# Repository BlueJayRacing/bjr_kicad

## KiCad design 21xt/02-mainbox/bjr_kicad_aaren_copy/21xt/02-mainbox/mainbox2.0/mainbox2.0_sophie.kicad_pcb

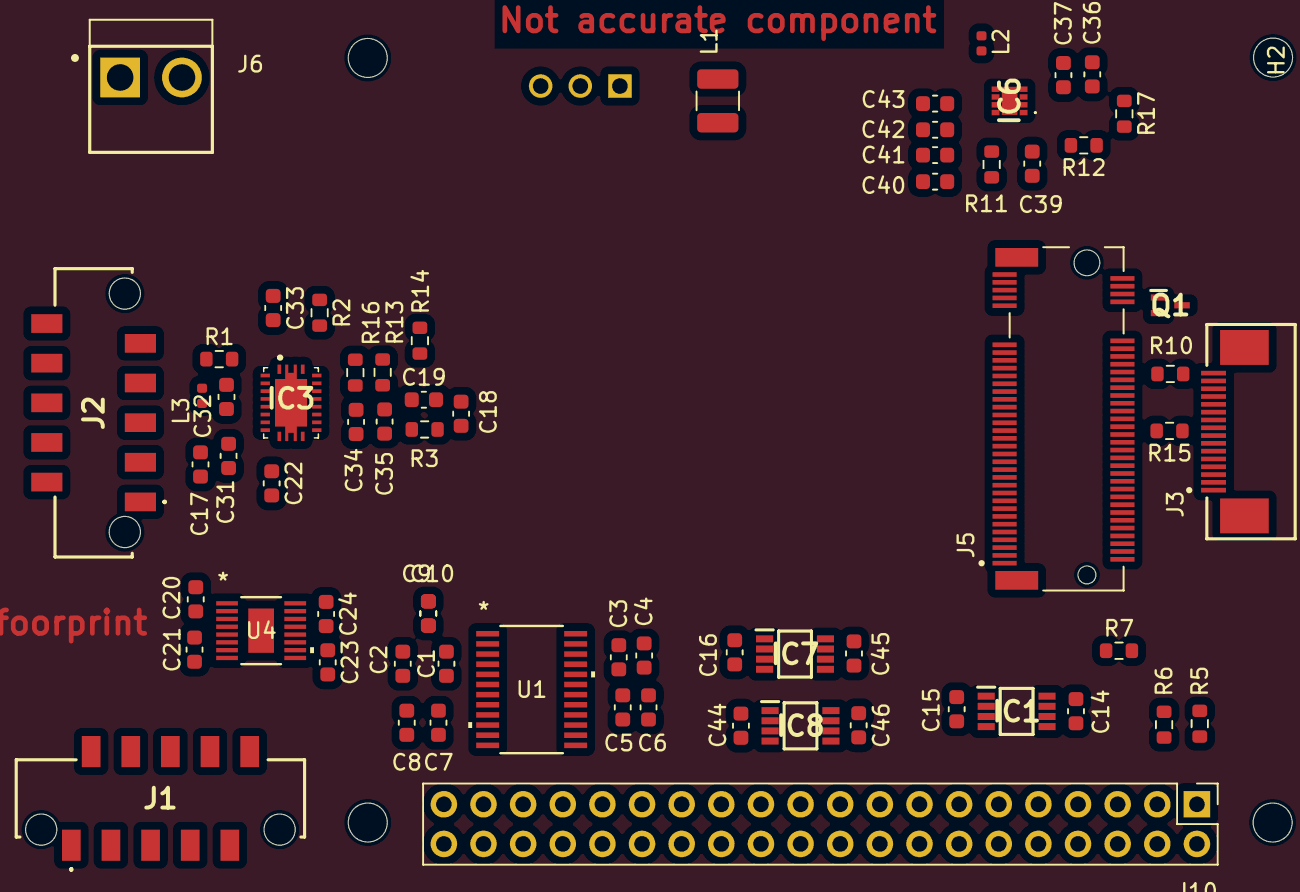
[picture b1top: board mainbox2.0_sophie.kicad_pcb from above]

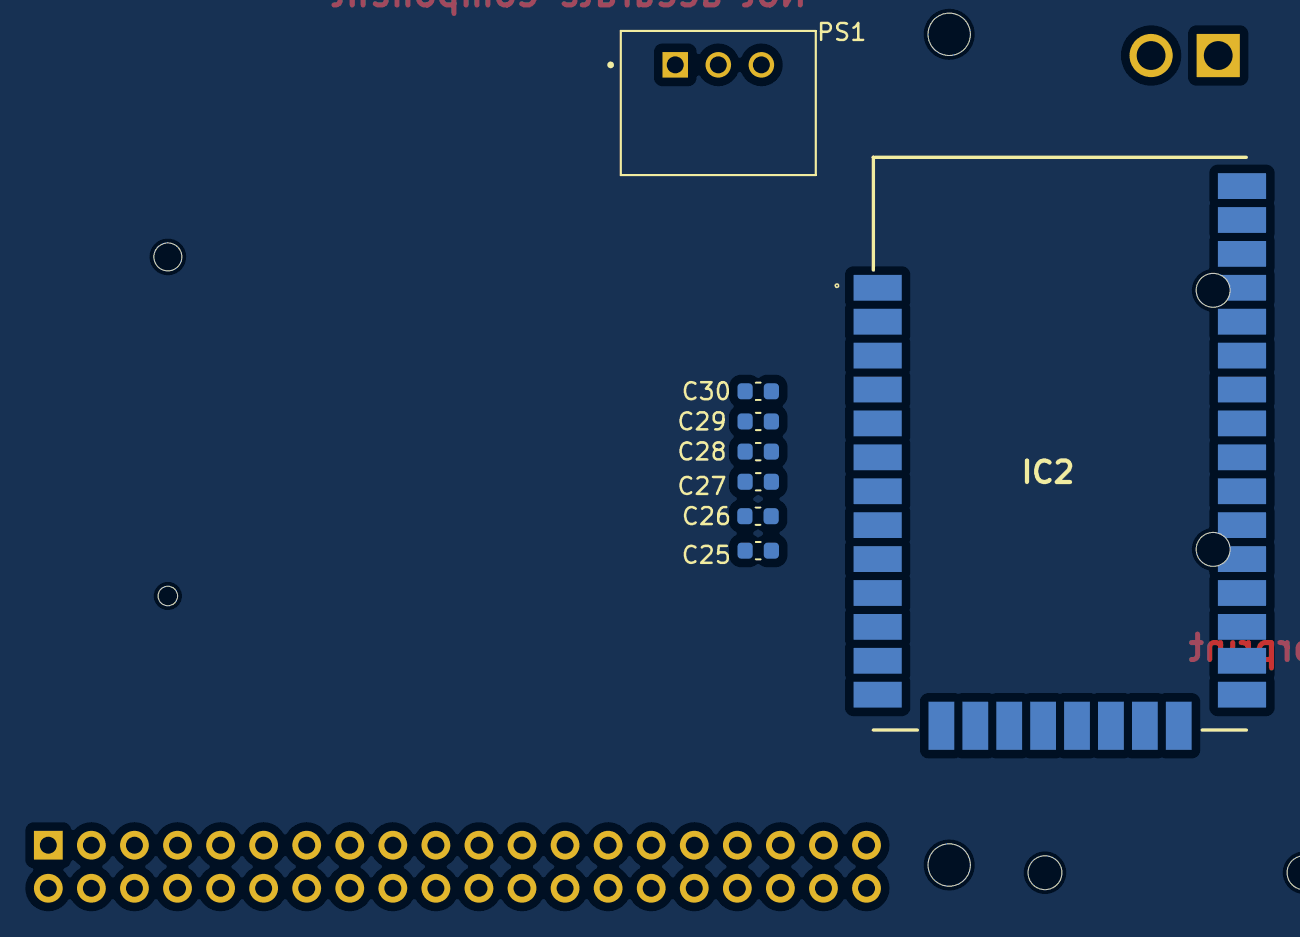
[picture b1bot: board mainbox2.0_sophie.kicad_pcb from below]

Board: 4 copper layers, 79 parts (8 on the bottom side), 57 nets, no tracks yet.

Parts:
C1, C3, C5, C7, C10, C14, C15, C16, C17, C20, C21, C23, C27, C31, C32, C44, C45, C46: 0.1uF; C_0603_1608Metric
C2, C4, C8, C24, C34: 1uF; C_0603_1608Metric
C6, C9, C25, C28, C36, C37, C40, C41, C42, C43: 10uF; C_0603_1608Metric
C18: 0.6nF; C_0603_1608Metric
C19: 3.1pF; C_0603_1608Metric
C22: 47nF; C_0603_1608Metric
C26: 4.7uF; C_0603_1608Metric
C29: 47pF; C_0603_1608Metric
C30: 8.2pF; C_0603_1608Metric
C33: 3.3uF; C_0603_1608Metric
C35: 47uF; C_0603_1608Metric
C39: 15pF; C_0603_1608Metric
H1, H2, H3, H4: MountingHole; MountingHole_2.5mm
IC1, IC7, IC8: SN74LVC2T45DCTTG4; SOP65P400X130-8N
IC2: XBP9X-DMUS-011; RLS397
IC3: TPS61088QRHLTQ1; BQ24123RHLT
IC6: AP3441LSHE-7B; AP3441LSHE7B
J1, J2: Conn_01x10; 908160010(picolex-10)
J3: Conn_01x16; SAMTEC_ZF5S-16-01-T-WT
J5: MDT275M02001; AMPHENOL_MDT275M02001
J6: Conn_01x02; JST_B2P-VH_LF__SN_(2 pin)
J10: Conn_02x20_Odd_Even; PinHeader_2x20_P2.54mm_Vertical
L1: 3.9uH; L_1210_3225Metric
L2: 22uH; L_0402_1005Metric
L3: 1.2uH; L_0402_1005Metric
PS1: R-78B3.3-1.5L; CONV_R-78B3.3-1.5
Q1: DMG1012T-7; SOT50P160X90-3N(DIODE)
R1: 225k; R_0603_1608Metric
R2: 49.9k; R_0603_1608Metric
R3: 125k; R_0603_1608Metric
R5, R6: 68; R_0603_1608Metric
R7, R15: 100k; R_0603_1608Metric
R10: 33; R_0603_1608Metric
R11, R17: 10k; R_0603_1608Metric
R12: 22k; R_0603_1608Metric
R13: 290k; R_0603_1608Metric
R14: 56k; R_0603_1608Metric
R16: 60k; R_0603_1608Metric
U1: AD7175-2BRUZ; RU_24_ADI
U4: LT6658AHMSE-5-PBF; LT6658AHMSE-2.5-PBF

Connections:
3V3: C5.1, C6.1, C14.2, C16.2, C44.2, IC1.8 (VCCB), IC7.1 (VCCA), IC8.1 (VCCA), J10.17, U1.16 (IOVDD)
3V3_PG: IC6.2 (PG), Q1.1 (G), R17.2
3V3_XBEE: C27.2, C28.2, C29.2, C30.2, IC2.2 (VCC), PS1.3 (+VOUT)
5.2V: C15.2, C25.1, C26.1, C36.1, C37.1, C45.2, C46.2, IC1.1 (VCCA), IC6.3 (VIN), IC7.8 (VCCB), IC8.8 (VCCB), J1.7, J6.2, J10.2, J10.4, L1.1, R17.1
5VADC/SENSOR: C7.2, C8.2, J2.6, U1.7 (AVDD1), U1.8 (AVDD2), U4.7 (VOUT2_S), U4.8 (VOUT2_F)
5VRef: C9.2, C10.2, C24.2, U1.3 (REF+), U4.12 (VOUT1_F), U4.13 (VOUT1_S)
7.5VBOOST: C23.1, C34.2, C35.2, IC3.14 (VOUT_1), IC3.15 (VOUT_2), IC3.16 (VOUT_3), R13.1, R16.1, U4.9 (*OD), U4.10 (VIN2), U4.11 (VIN1), U4.14 (VIN)
ANI1: J2.1, U1.22 (AIN1)
ANI2: J2.2, U1.23 (AIN2)
ANI3: J2.3, U1.24 (AIN3)
ANI4: J2.4, U1.1 (AIN4)
CS: J10.24, U1.14 (*CS)
DIGITAL_INPUT_1: IC8.7 (B1), J2.7
DIGITAL_INPUT_2: IC8.6 (B2), J2.8
DIGITAL_INPUT_3: IC7.7 (B1), J2.9
DIGITAL_INPUT_4: IC7.6 (B2), J2.10
DIGITAL_OUTPUT_1: IC8.2 (A1), J10.3
DIGITAL_OUTPUT_2: IC8.3 (A2), J10.5
DIN: J10.19, U1.12 (DIN)
DINXBee: IC2.4 (DIN/DIO14/~CONFIG), R6.1, R7.1
DOUT: J10.21, U1.11 (DOUT/*RDY)
DOUTXBee: IC2.3 (DIO13/DOUT), R5.2
GND: C1.2, C2.2, C3.1, C4.1, C5.2, C6.2, C7.1, C8.1, C9.1, C10.1, C14.1, C15.1, C16.1, C17.2, C18.2, C19.2, C20.1, C21.1, C22.2, C23.2, C24.1, C25.2, C26.2, C27.1, C28.1, C29.1, C30.1, C31.2, C33.1, C34.1, C35.1, C36.2, C37.2, C40.2, C41.2, C42.2, C43.2, C44.1, C45.1, C46.1, IC1.4 (GND), IC1.5 (DIR), IC2.1 (GND_1), IC2.11 (GND_2), IC2.13 (GND_3), IC2.22 (GND_4), IC2.35 (GND_5), IC3.11 (NC_1), IC3.12 (NC_2), IC3.20 (AGND), IC3.21 (PGND_1), IC3.22 (PGND_2), IC3.23 (PGND_3), IC3.24 (PGND_4), IC3.25 (PGND_5), IC3.26 (PGND_6), IC3.27 (PGND_7), IC6.4 (PGND), IC6.8 (SGND), IC6.9 (EP), IC7.4 (GND), IC7.5 (DIR), IC8.4 (GND), IC8.5 (DIR), J1.8, J2.5, J3.12, J5.1, J5.3, J5.9, J5.15, J5.21, J5.27, J5.33, J5.39, J5.45, J5.51, J5.57, J5.71, J5.73, J5.75, J6.1, J10.6, J10.9, PS1.2 (GND), R2.1, R12.1, R14.2, R15.2, U1.2 (REF-), U1.6 (AVSS), U1.15 (*SYNC/*ERROR), U1.17 (DGND), U4.1 (GND), U4.2 (GND), U4.6 (GND), U4.EPAD
IN1(3.3V): IC1.7 (B1), J10.11
IN1(5V): IC1.2 (A1), J1.9
IN2(3.3V): IC1.6 (B2), J10.13
IN2(5V): IC1.3 (A2), J1.10
unnamed: C18.1, R3.2
unnamed: C32.1, IC3.8 (BOOT)
unnamed: C19.1, IC3.18 (COMP), R3.1
unnamed: IC3.17 (FB), R13.2, R14.1, R16.2
unnamed: IC3.3 (FSW), R1.2
unnamed: IC3.19 (ILIM), R2.2
unnamed: C22.1, IC3.10 (SS)
unnamed: C32.2, IC3.4 (SW_1), IC3.5 (SW_2), IC3.6 (SW_3), IC3.7 (SW_4), L3.2, R1.1
unnamed: C33.2, IC3.1 (VCC)
unnamed: C39.1, C39.2, IC6.1 (FB), R11.2, R12.2
unnamed: IC6.6 (LX), L2.1
unnamed: J3.16, R10.1
unnamed: J10.8, R5.1
unnamed: J10.10, R6.2
unnamed: L1.2, PS1.1 (+VIN)
unnamed: C1.1, C2.1, U1.5 (REGCAPA)
unnamed: C3.2, C4.2, U1.18 (REGCAPD)
unnamed: C20.2, U4.3 (BYPASS)
unnamed: C21.2, U4.5 (NR)
PCIE0 TX+: J3.10, J5.49
PCIE0 TX-: J3.11, J5.47
PCIE_CLKREQ_N: J3.15, J5.52
PCIE_PWR_EN: IC6.7 (EN), J3.13, R15.1
PCIE_RST_B: Q1.3 (D), R10.2
PCIE_RST_B_SW: J5.50, Q1.2 (S)
SCLK: J10.23, U1.13 (SCLK)
STEERING_WHEEL_RX: J1.6, J10.29
STEERING_WHEEL_TX: J1.5, J10.27
VCC3V3: C40.1, C41.1, C42.1, C43.1, J5.2, J5.4, J5.12, J5.14, J5.16, J5.18, J5.70, J5.72, J5.74, L2.2, R11.1
Vin: C17.1, C31.1, IC3.2 (EN), IC3.9 (VIN), L3.1

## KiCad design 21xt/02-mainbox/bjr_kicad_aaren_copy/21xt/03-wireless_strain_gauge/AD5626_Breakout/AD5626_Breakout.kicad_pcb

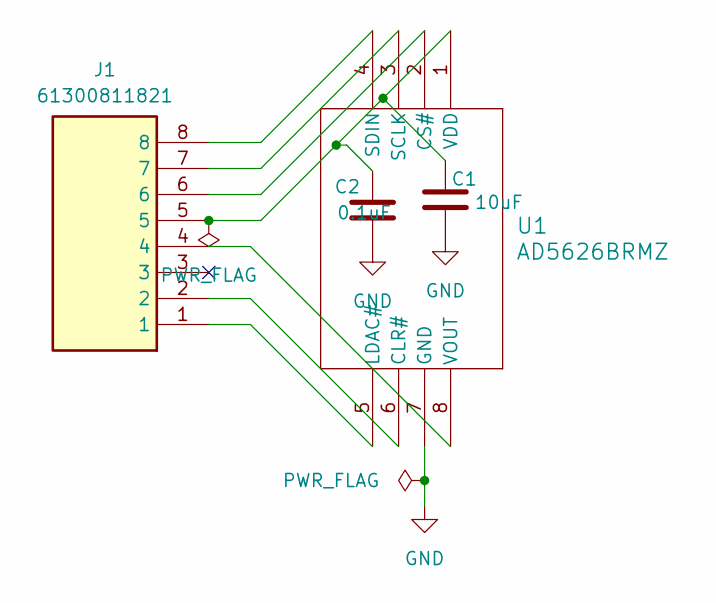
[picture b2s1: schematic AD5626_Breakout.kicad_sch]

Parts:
C1: 10uF; C_0603_1608Metric_Pad1.08x0.95mm_HandSolder
C2: 0.1uF; C_0603_1608Metric_Pad1.08x0.95mm_HandSolder
J1: 61300811821; RHDR8W60P0X254_1X8_2082X250X850P; Mouser Part Number 710-61300811821
U1: AD5626BRMZ; AD5626

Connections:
GND: C1.2, C2.2, U1.7 (GND)
unnamed: J1.2, U1.6 (CLR#)
unnamed: J1.6, U1.2 (CS#)
unnamed: J1.1, U1.5 (LDAC#)
unnamed: J1.7, U1.3 (SCLK)
unnamed: J1.8, U1.4 (SDIN)
unnamed: C1.1, C2.1, J1.5, U1.1 (VDD)
unnamed: J1.4, U1.8 (VOUT)

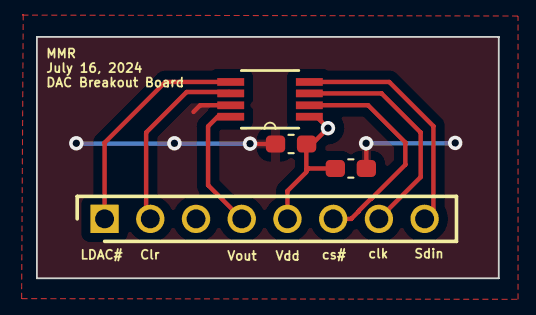
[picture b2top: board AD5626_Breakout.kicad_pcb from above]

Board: 2 copper layers, 25.7 x 13.4 mm, 4 parts (0 on the bottom side), 8 nets.

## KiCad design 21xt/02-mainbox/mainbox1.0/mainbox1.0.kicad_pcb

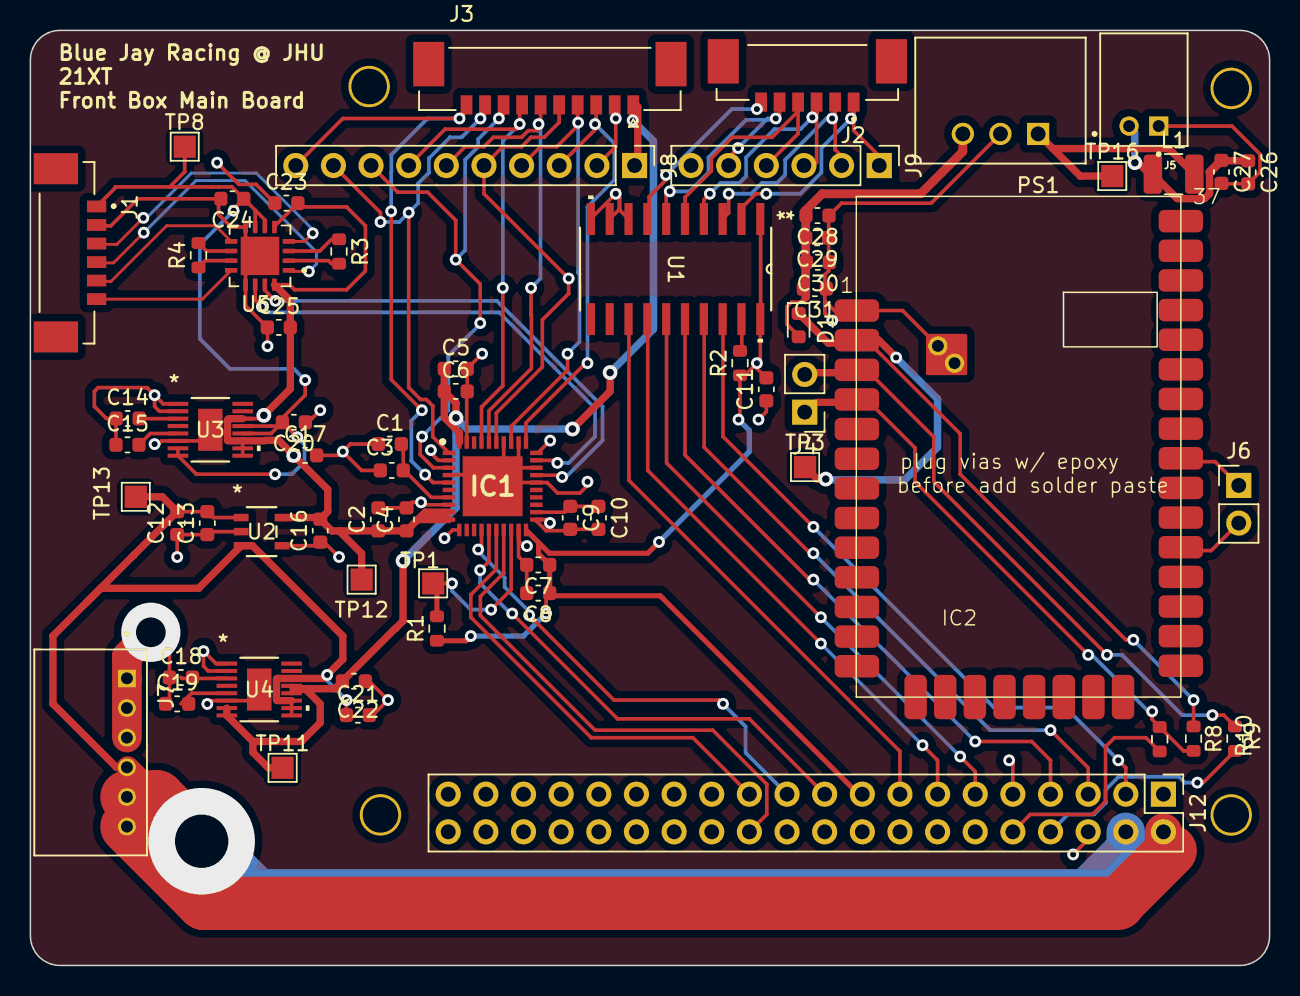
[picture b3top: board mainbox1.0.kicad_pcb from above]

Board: 4 copper layers, 83.6 x 63.1 mm, 69 parts (0 on the bottom side), 58 nets.

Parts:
C1, C10, C12, C20, C22: 1uF; C_0603_1608Metric
C2, C5, C8, C26, C29: 10uF; C_0603_1608Metric
C3, C4, C6, C7, C9, C11, C13, C14, C15, C17, C18, C19, C21, C23, C24, C25: 0.1uF; C_0603_1608Metric
C16: 2.2uF; C_0603_1608Metric
C27: 4.7; C_0603_1608Metric
C28: 0.1; C_0603_1608Metric
C30: 47pF; C_0603_1608Metric
C31: 8.2pF; C_0603_1608Metric
D1: D_Schottky; D_0603_1608Metric
H1, H2, H3, H4: MountingHole; 2.35mm_mounting_hole
IC1: AD7175-8BCPZ-RL7; QFN50P600X600X80-41N-D
IC2: XBP9X-DMUS-011; xbee sx 900
J1, J2: Conn_01x06; MOLEX_0533980671 (1x6)
J3: Conn_01x10; MOLEX_533981071 (1x10)
J4, J6: Conn_01x02; PinHeader_1x02_P2.54mm_Vertical
J5: Conn_01x02; JST_S2B-PH-K-S_LF__SN_
J7: Conn_01x06; JST_S6B-PH-K-S_LF__SN_(1x6)
J8: Conn_01x10; PinHeader_1x10_P2.54mm_Vertical
J9: Conn_01x06; PinHeader_1x06_P2.54mm_Vertical
J12: Conn_02x20_Odd_Even; PinHeader_2x20_P2.54mm_Vertical
L1: 3.9uH; L_1210_3225Metric
PS1: R-78B3.3-1.5L; CONV_R-78B3.3-1.5
R1, R2: 10k; R_0603_1608Metric
R3, R4: 200; R_0603_1608Metric
R8, R9: 68; R_0603_1608Metric
R10: 100k; R_0603_1608Metric
TP1, TP3, TP8, TP11, TP12, TP13, TP16: TestPoint; TestPoint_Pad_1.5x1.5mm
U1: SN74LVC245AN
U2: TPS78326DDCT
U3: LT6658AHMSE-2.5-PBF
U4: LT6658AHMSE-5-PBF; LT6658AHMSE-2.5-PBF
U5: AD8222ACPZ-R7

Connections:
2.5V: C20.2, C24.1, J1.1, TP8.1, U3.7 (VOUT2_S), U3.8 (VOUT2_F), U3.12 (VOUT1_F), U3.13 (VOUT1_S), U5.6 (REF1), U5.7 (REF2)
3V3: C7.1, C8.1, C11.2, IC1.20 (IOVDD), J12.17, R1.1, R2.1, U1.1 (DIR), U1.20 (VCC)
5.2V: C12.2, C13.2, C21.1, J7.4, J7.5, J7.6, J12.2, J12.4, TP13.1, U2.1 (IN), U2.3 (EN), U4.9 (*OD), U4.10 (VIN2), U4.11 (VIN1), U4.14 (VIN)
5VADC: C2.1, C4.1, C16.2, C17.1, C23.2, C25.2, IC1.9 (AVDD1), IC1.10 (AVDD2), TP12.1, U2.5 (OUT), U3.9 (*OD), U3.10 (VIN2), U3.11 (VIN1), U3.14 (VIN), U5.5 (+VS), U5.16 (+VS__1)
5VASupply/Ref: C5.1, C6.1, C22.2, IC1.40 (REF+), J3.1, J8.1, TP11.1, U4.7 (VOUT2_S), U4.8 (VOUT2_F), U4.12 (VOUT1_F), U4.13 (VOUT1_S)
5VXbee: C26.1, C27.1, J5.2, L1.1
ANI1: IC1.3 (AIN1/REF2+), J3.8, J8.8
ANI3: IC1.5 (AIN3), J3.10, J8.10
ANI9: IC1.31 (AIN9), J3.3, J8.3
ANI11: IC1.33 (AIN11), J3.4, J8.4
ANI13: IC1.35 (AIN13), J3.5, J8.5
ANI14: IC1.36 (AIN14), J3.6, J8.6
ANI15: IC1.37 (AIN15), J3.7, J8.7
ANI16: IC1.1 (AIN16), J3.9, J8.9
CS: IC1.17 (~CS), J12.24
DIN: IC1.15 (DIN), J12.19
DINXBee: IC2.4 (DIN/DIO14/~CONFIG), J4.1, R9.1, R10.1
DO1: J12.3, U1.18 (B1)
DO2: J12.5, U1.17 (B2)
DO3: J12.7, U1.16 (B3)
DO4: J12.11, U1.15 (B4)
DO5: J12.13, U1.14 (B5)
DO6: J12.15, U1.13 (B6)
DOUT: IC1.14 (DOUT/~RDY), J12.21
DOUTXBee: IC2.3 (DIO13/DOUT), J4.2, R8.2
DS1: J2.1, J9.1, U1.2 (A1)
DS2: J2.2, J9.2, U1.3 (A2)
DS3: J2.3, J9.3, U1.4 (A3)
DS4: J2.4, J9.4, U1.5 (A4)
DS5: J2.5, J9.5, U1.6 (A5)
DS6: J2.6, J9.6, U1.7 (A6)
GND: C1.1, C2.2, C3.1, C4.2, C5.2, C6.2, C7.2, C8.2, C9.2, C10.2, C11.1, C12.1, C13.1, C14.1, C15.1, C16.1, C17.2, C18.1, C19.1, C20.1, C21.2, C22.1, C23.1, C24.2, C25.1, C26.2, C27.2, C28.1, C29.1, C30.1, C31.1, IC1.2 (AIN0/REF2-), IC1.4 (AIN2), IC1.8 (AVSS), IC1.11 (PDSW), IC1.19 (~SYNC), IC1.21 (DGND), IC1.26 (AIN4), IC1.28 (AIN6), IC1.30 (AIN8), IC1.32 (AIN10), IC1.34 (AIN12), IC1.39 (REF-), IC1.41 (EP), IC2.1 (GND_1), IC2.38 (GND_6), J1.2, J3.2, J5.1, J7.1, J7.2, J7.3, J8.2, J12.6, J12.9, PS1.2 (GND), U1.8 (A7), U1.9 (A8), U1.10 (GND), U2.2 (GND), U2.4 (GND), U3.1 (GND), U3.2 (GND), U3.6 (GND), U3.EPAD, U4.1 (GND), U4.2 (GND), U4.6 (GND), U4.EPAD, U5.8 (-VS__1), U5.13 (-VS), U5.17 (EP)
unnamed: C28.2, C29.2, C30.2, C31.2, D1.2 (A), PS1.3 (+VOUT)
unnamed: C1.2, C3.2, IC1.7 (REGCAPA)
unnamed: C9.1, C10.1, IC1.22 (REGCAPD)
unnamed: IC1.18 (~ERROR), R1.2, TP1.1
unnamed: IC2.29 (DIO6/~RTS), J6.1
unnamed: IC2.26 (DIO9/ON/~SLEEP), J6.2
unnamed: J12.8, R8.1
unnamed: J12.10, R9.2
unnamed: L1.2, PS1.1 (+VIN), TP16.1
unnamed: R2.2, U1.19 (*OE)
unnamed: C14.2, U3.3 (BYPASS)
unnamed: C15.2, U3.5 (NR)
unnamed: C18.2, U4.3 (BYPASS)
unnamed: C19.2, U4.5 (NR)
unnamed: R3.2, U5.2 (RG1)
unnamed: R3.1, U5.3 (RG1__1)
unnamed: R4.2, U5.10 (RG2)
unnamed: R4.1, U5.11 (RG2__1)
SCLK: IC1.16 (SCLK), J12.23
SG1: IC1.27 (AIN5), U5.15 (OUT1)
SG1+: J1.3, U5.4 (+IN1)
SG1-: J1.4, U5.1 (-IN1)
SG2: IC1.29 (AIN7), U5.14 (OUT2)
SG2+: J1.5, U5.9 (+IN2)
SG2-: J1.6, U5.12 (-IN2)
VOUT: D1.1 (K), IC2.2 (VCC), R10.2, TP3.1

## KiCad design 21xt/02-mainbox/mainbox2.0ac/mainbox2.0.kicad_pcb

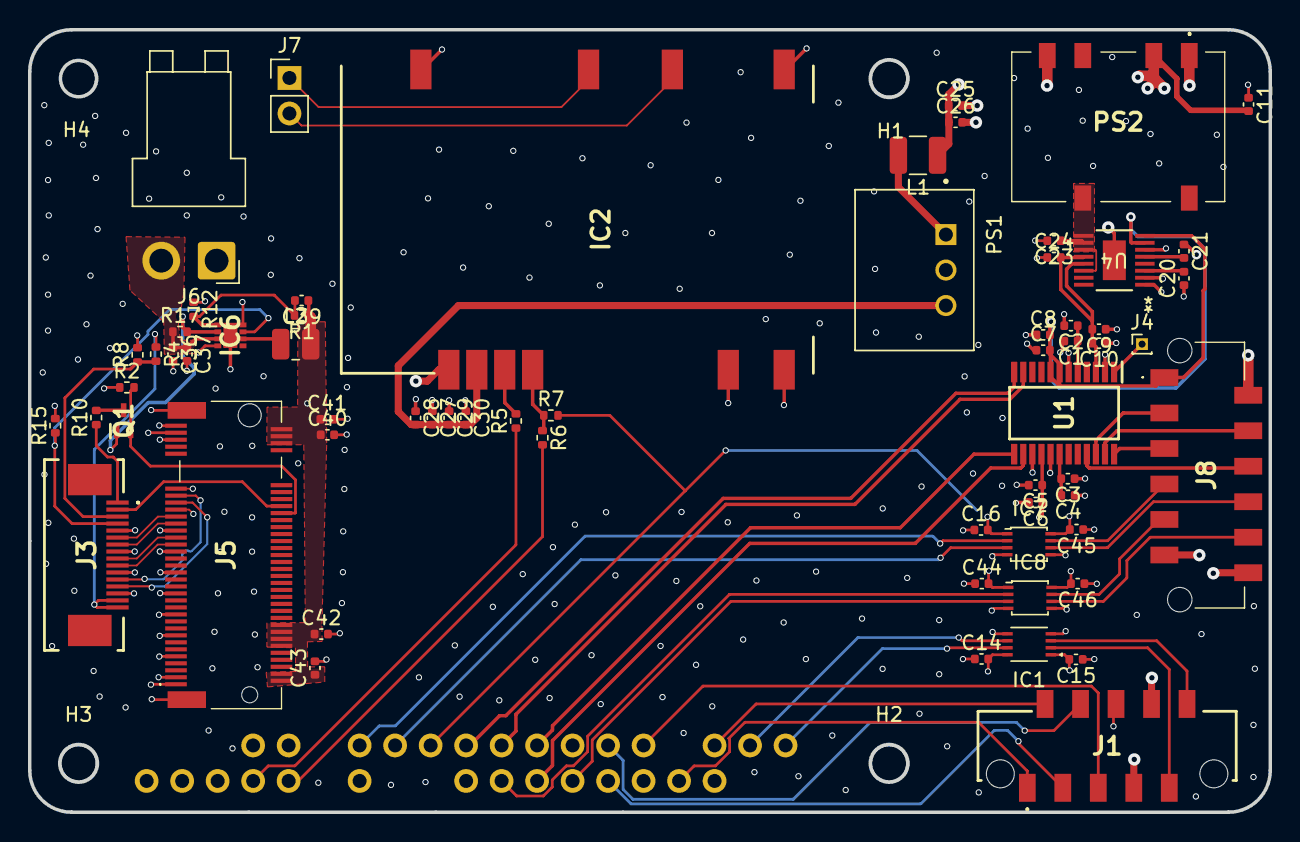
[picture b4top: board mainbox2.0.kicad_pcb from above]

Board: 4 copper layers, 88.8 x 56.0 mm, 69 parts (1 on the bottom side), 62 nets.

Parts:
C1, C3, C5, C7, C10, C11, C14, C15, C16, C20, C21, C23, C27, C44, C45, C46: 0.1uF; C_0402_1005Metric
C2, C4, C8, C24: 1uF; C_0402_1005Metric
C6, C9, C25, C28, C36, C37, C40, C41, C42, C43: 10uF; C_0402_1005Metric
C26: 4.7uF; C_0402_1005Metric
C29: 47pF; C_0402_1005Metric
C30: 8.2pF; C_0402_1005Metric
C39: 15pF; C_0402_1005Metric
H1, H2, H3, H4: MountingHole; MountingHole_2.5mm
IC1, IC7, IC8: SN74LVC2T45DCTTG4; VSSOP-8_2.4x2.1mm_P0.5mm
IC2: XBP9X-DMUS-011; RLS397
IC6: AP3441LSHE-7B; AP3441LSHE7B
J1: Conn_01x10; 908160010
J3: Conn_01x16; ZF5S1601TWT
J4: Conn_01x01_Pin; PinHeader_1x01_P1.00mm_Vertical
J5: MDT275M02001
J6: Conn_01x02; JST_VH_B2PS-VH_1x02_P3.96mm_Horizontal
J7: Conn_01x02; PinHeader_1x02_P2.54mm_Vertical
J8: Conn_01x12; 908160012
J10: Conn_02x20_Odd_Even; PinHeader_2x20_P2.54mm_Vertical
L1: 3.9uH; L_1210_3225Metric
L2: 2.2uH; L_1008_2520Metric
PS1: R-78B3.3-1.5L; CONV_R-78B3.3-1.5
PS2: R2D12-0509; R2D120509
Q1: DMG1012T-7; SOT50P160X90-3N
R1, R17: 10k; R_0402_1005Metric
R2: 2.2k; R_0402_1005Metric
R4: 3k6; R_0402_1005Metric
R5, R6: 68; R_0402_1005Metric
R7, R15: 100k; R_0402_1005Metric
R8: 6k8; R_0402_1005Metric
R10: 33; R_0402_1005Metric
R12: 45k; R_0402_1005Metric
U1: AD7175-2BRUZ; SOP65P640X120-24N
U4: LT6658AHMSE-5-PBF; LT6658AHMSE-2.5-PBF

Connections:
3V3: C5.1, C6.1, C14.2, C16.2, C44.2, IC1.8 (VCCB), IC7.1 (VCCA), IC8.1 (VCCA), J10.17, R7.2, U1.16 (IOVDD)
3V3_PG: IC6.2 (PG), Q1.1 (G), R17.2
3V3_XBEE: C27.2, C28.2, C29.2, C30.2, IC2.2 (VCC), PS1.3 (+VOUT)
5.2V: C11.2, C15.2, C25.1, C26.1, C36.1, C37.1, C45.2, C46.2, IC1.1 (VCCA), IC6.3 (VIN), IC7.8 (VCCB), IC8.8 (VCCB), J1.7, J6.2, J8.11, J10.2, J10.4, L1.1, PS2.2 (+VIN), R17.1
5V PCIE: J3.15, J3.16, R4.1
5VADC/SENSOR: C7.2, C8.2, J8.1, U1.7 (AVDD1), U1.8 (AVDD2), U4.7 (VOUT2_S), U4.8 (VOUT2_F)
5VRef: C9.2, C10.2, C24.2, U1.3 (REF+), U4.12 (VOUT1_F), U4.13 (VOUT1_S)
9V: C23.1, PS2.7 (+VOUT), U4.9 (*OD), U4.10 (VIN2), U4.11 (VIN1), U4.14 (VIN)
ADC_SPI_DIN: J10.19, U1.12 (DIN)
ADC_SPI_DOUT: J10.21, U1.11 (DOUT/*RDY)
AIN0: J8.6, U1.21 (AIN0)
AIN1: J8.3, U1.22 (AIN1)
AIN2: J8.4, U1.23 (AIN2)
AIN3: J8.5, U1.24 (AIN3)
AIN4: J4.1, U1.1 (AIN4)
DIGITAL_INPUT_1: IC8.6 (B2), J8.10
DIGITAL_INPUT_2: IC8.7 (B1), J8.9
DIGITAL_INPUT_3: IC7.6 (B2), J8.8
DIGITAL_INPUT_4: IC7.7 (B1), J8.7
DIGITAL_OUTPUT_1: IC8.3 (A2), J10.26
DIGITAL_OUTPUT_2: IC8.2 (A1), J10.22
DIGITAL_OUTPUT_3: IC7.3 (A2), J10.15
DIGITAL_OUTPUT_4: IC7.2 (A1), J10.13
DINXBee: IC2.4 (DIN/DIO14/~CONFIG), R6.1, R7.1
DOUTXBee: IC2.3 (DIO13/DOUT), R5.2
GNDA: C1.2, C2.2, C3.1, C4.1, C5.2, C6.2, C7.1, C8.1, C9.1, C10.1, C11.1, C14.1, C15.1, C16.1, C20.1, C21.1, C23.2, C24.1, C25.2, C26.2, C27.1, C28.1, C29.1, C30.1, C36.2, C37.2, C40.2, C41.2, C42.2, C43.2, C44.1, C45.1, C46.1, IC1.4 (GND), IC1.5 (DIR), IC2.1 (GND_1), IC2.11 (GND_2), IC2.13 (GND_3), IC2.22 (GND_4), IC2.35 (GND_5), IC6.4 (PGND), IC6.8 (SGND), IC6.9 (EP), IC7.4 (GND), IC7.5 (DIR), IC8.4 (GND), IC8.5 (DIR), J1.8, J3.5, J3.8, J3.11, J3.14, J5.1, J5.3, J5.9, J5.15, J5.21, J5.27, J5.33, J5.39, J5.45, J5.51, J5.57, J5.71, J5.73, J5.75, J5.MP1, J5.MP2, J6.1, J8.2, J8.12, J10.6, J10.9, J10.14, J10.20, J10.25, J10.30, J10.34, PS1.2 (GND), PS2.1 (-VIN), PS2.5 (-VOUT), R2.1, R8.2, R12.1, R15.2, U1.2 (REF-), U1.6 (AVSS), U1.15 (*SYNC/*ERROR), U1.17 (DGND), U4.1 (GND), U4.2 (GND), U4.6 (GND), U4.EPAD
IN1(3.3V): IC1.7 (B1), J10.37
IN1(5V): IC1.2 (A1), J1.9
IN2(3.3V): IC1.6 (B2), J10.35
IN2(5V): IC1.3 (A2), J1.10
NAVIN: J1.2, J10.33
NAVOUT: J1.1, J10.32
unnamed: IC2.29 (DIO6/~RTS), J7.1
unnamed: IC2.26 (DIO9/ON/~SLEEP), J7.2
unnamed: C39.2, IC6.1 (FB), R1.2, R12.2
unnamed: IC6.6 (LX), L2.1
unnamed: J3.1, R10.1
unnamed: J10.8, R5.1
unnamed: J10.10, R6.2
unnamed: L1.2, PS1.1 (+VIN)
unnamed: C1.1, C2.1, U1.5 (REGCAPA)
unnamed: C3.2, C4.2, U1.18 (REGCAPD)
unnamed: C20.2, U4.3 (BYPASS)
unnamed: C21.2, U4.5 (NR)
PCIE0 RX+: J3.9, J5.43
PCIE0 RX-: J3.10, J5.41
PCIE0 TX+: J3.6, J5.49
PCIE0 TX-: J3.7, J5.47
PCIE CLK+: J3.12, J5.55
PCIE CLK-: J3.13, J5.53
PCIE_CLKREQ_N: J3.2, J5.52
PCIE_DET_WAKE: J3.3, R4.2, R8.1
PCIE_PWR_EN: IC6.7 (EN), J3.4, R15.1
PCIE_RST_B: Q1.3 (D), R10.2
PCIE_RST_B_SW: J5.50, Q1.2 (S), R2.2
POWER_BOARD_PORT_RXD: J1.3, J10.28
POWER_BOARD_PORT_TXD: J1.4, J10.27
RPi_SPI_CS: J10.24, U1.14 (*CS)
SCLK: J10.23, U1.13 (SCLK)
STEERING_WHEEL_PORT_RXD: J1.5, J10.29
STEERING_WHEEL_PORT_TXD: J1.6, J10.7
VCC3V3: C39.1, C40.1, C41.1, C42.1, C43.1, J5.2, J5.4, J5.12, J5.14, J5.16, J5.18, J5.70, J5.72, J5.74, L2.2, R1.1

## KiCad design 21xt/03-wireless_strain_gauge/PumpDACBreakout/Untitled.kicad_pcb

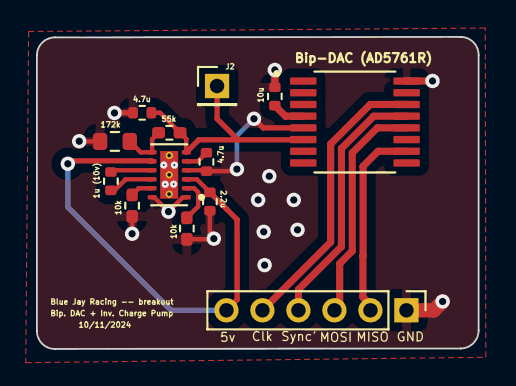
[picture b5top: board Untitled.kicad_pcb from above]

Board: 2 copper layers, 24.5 x 17.3 mm, 13 parts (0 on the bottom side), 14 nets.

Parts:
1u (10v): 1u (10V); R_0402_1005Metric
4.7u, 4.7u#2: 4.7u; R_0402_1005Metric
10k: 10k; R_0402_1005Metric_Pad0.72x0.64mm_HandSolder
55k: 55k; R_0402_1005Metric_Pad0.72x0.64mm_HandSolder
Bip-DAC (AD5761R): AD5721RBRUZ; AD5721
C1: 10u; R_0402_1005Metric
C4: 2.2u; R_0402_1005Metric
J1: Conn_01x06; PinHeader_1x06_P2.00mm_Vertical
J2: Conn_01x01; PinHeader_1x01_P2.00mm_Vertical
PS1: LM27762DSSR; LM27762DSST
R2: 10k; R_0402_1005Metric_Pad0.72x0.64mm_HandSolder
R5: 172k; R_0603_1608Metric

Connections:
-5v: 4.7u.1, 55k.1, Bip-DAC (AD5761R).6 (VSS), J2.1, PS1.6 (OUT-)
GND: 4.7u.2, 4.7u#2.2, 10k.2, Bip-DAC (AD5761R).5 (AGND), Bip-DAC (AD5761R).16 (DGND), C1.1, C4.1, J1.1, PS1.1 (PGOOD), PS1.4 (GND), PS1.12 (EN+), PS1.13 (PAD), R2.2, R5.2
MISO: Bip-DAC (AD5761R).10 (SDO), J1.2
MOSI: Bip-DAC (AD5761R).12 (SDI), J1.3
unnamed: Bip-DAC (AD5761R).4 (VREFIN/VREFOUT), C1.2
unnamed: 1u (10v).1, PS1.10 (C1+)
unnamed: 1u (10v).2, PS1.9 (C1-)
unnamed: 4.7u#2.1, PS1.5 (CP)
unnamed: PS1.2 (FB+), R2.1
unnamed: 55k.2, PS1.7 (FB-), R5.1
unnamed: 10k.1, PS1.11 (OUT+)
Sclk: Bip-DAC (AD5761R).14 (SCLK), J1.5
Sync': Bip-DAC (AD5761R).13 (~SYNC), J1.4
Vin: Bip-DAC (AD5761R).8 (VDD), Bip-DAC (AD5761R).15 (DVCC), C4.2, J1.6, PS1.3 (VIN), PS1.8 (EN-)
